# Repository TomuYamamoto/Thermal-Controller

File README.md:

# Thermal-Controller

ペルチェ素子を用いて試料を冷却する。

温度測定がサーミスタを用いている。サーミスタはジャンパ線を使って接続しているのでちょっとした衝撃などで変化しやすい。

P制御により目標温度値へと制御する。(PID制御しようとした形跡あるけど気にしない。)
目標温度値は20℃前後が目安。（電源によって変化するかも？）

回路設計はフリーの回路設計ソフトであるKiCad(version5.1.10)によって設計した。version6.0以降だと仕様の変更に伴い回路図が変化する可能性有。

電源について、ペルチェ素子は安定化電源などを用いて12V（最大定格15.4V、6.0A）を、Arduino Uno Rev3にはDCジャックに接続する。
（使用ペルチェ：https://akizukidenshi.com/catalog/g/gI-00485/ ）

排熱はヒートシンクとDCファンを使用。DCファンの制御はせずにそのまま5Vを接続している。

改善案としてはLCDを用いたモニタリング、DCファンの制御などを考える。

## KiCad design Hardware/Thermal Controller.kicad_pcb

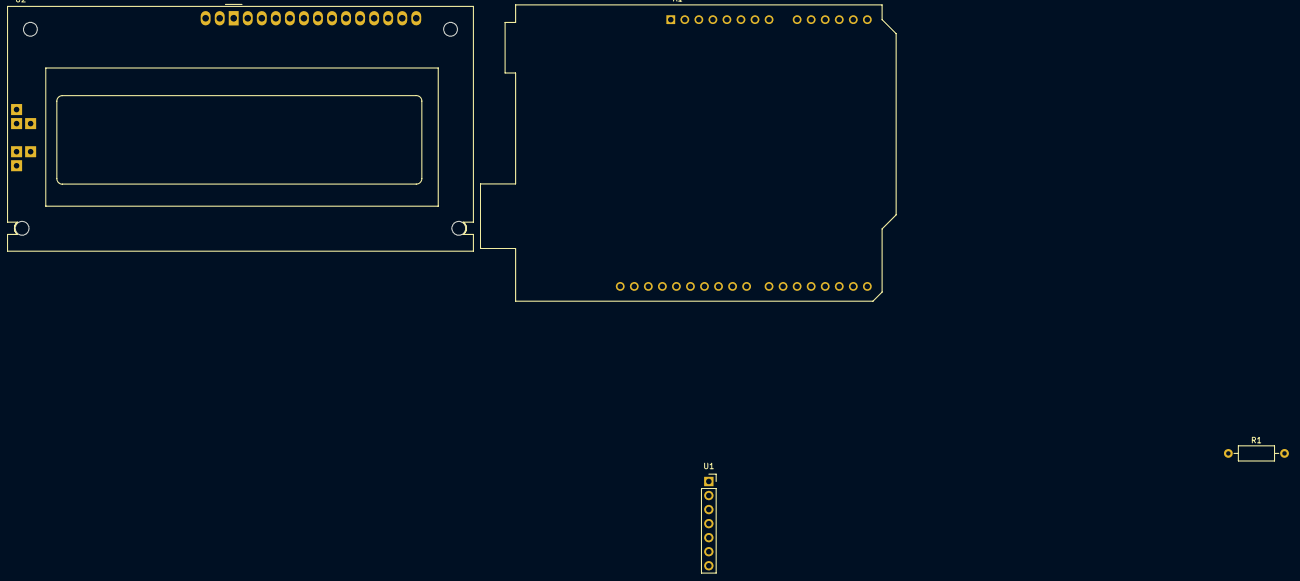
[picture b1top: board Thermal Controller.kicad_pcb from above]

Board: 2 copper layers, 4 parts (0 on the bottom side), 11 nets, no tracks yet.

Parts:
A1: Arduino_UNO_R3
R1: R; R_Axial_DIN0207_L6.3mm_D2.5mm_P10.16mm_Horizontal
U1: TB6643KQ; PinSocket_1x07_P2.54mm_Vertical
U2: RC1602A

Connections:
A_Thermistor: A1.9, R1.2
GND: A1.6, R1.1, U1.4, U2.1
LCD_D1: A1.25, U2.11
LCD_D2: A1.26, U2.12
LCD_D3: A1.27, U2.13
LCD_D4: A1.28, U2.14
LCD_E: A1.23, U2.6
LCD_RS: A1.22, U2.4
unnamed: A1.7, A1.29
PWM_Peltier1: A1.20, U1.1
PWM_Peltier2: A1.21, U1.2

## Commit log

2022-01-06 Create Hardware
